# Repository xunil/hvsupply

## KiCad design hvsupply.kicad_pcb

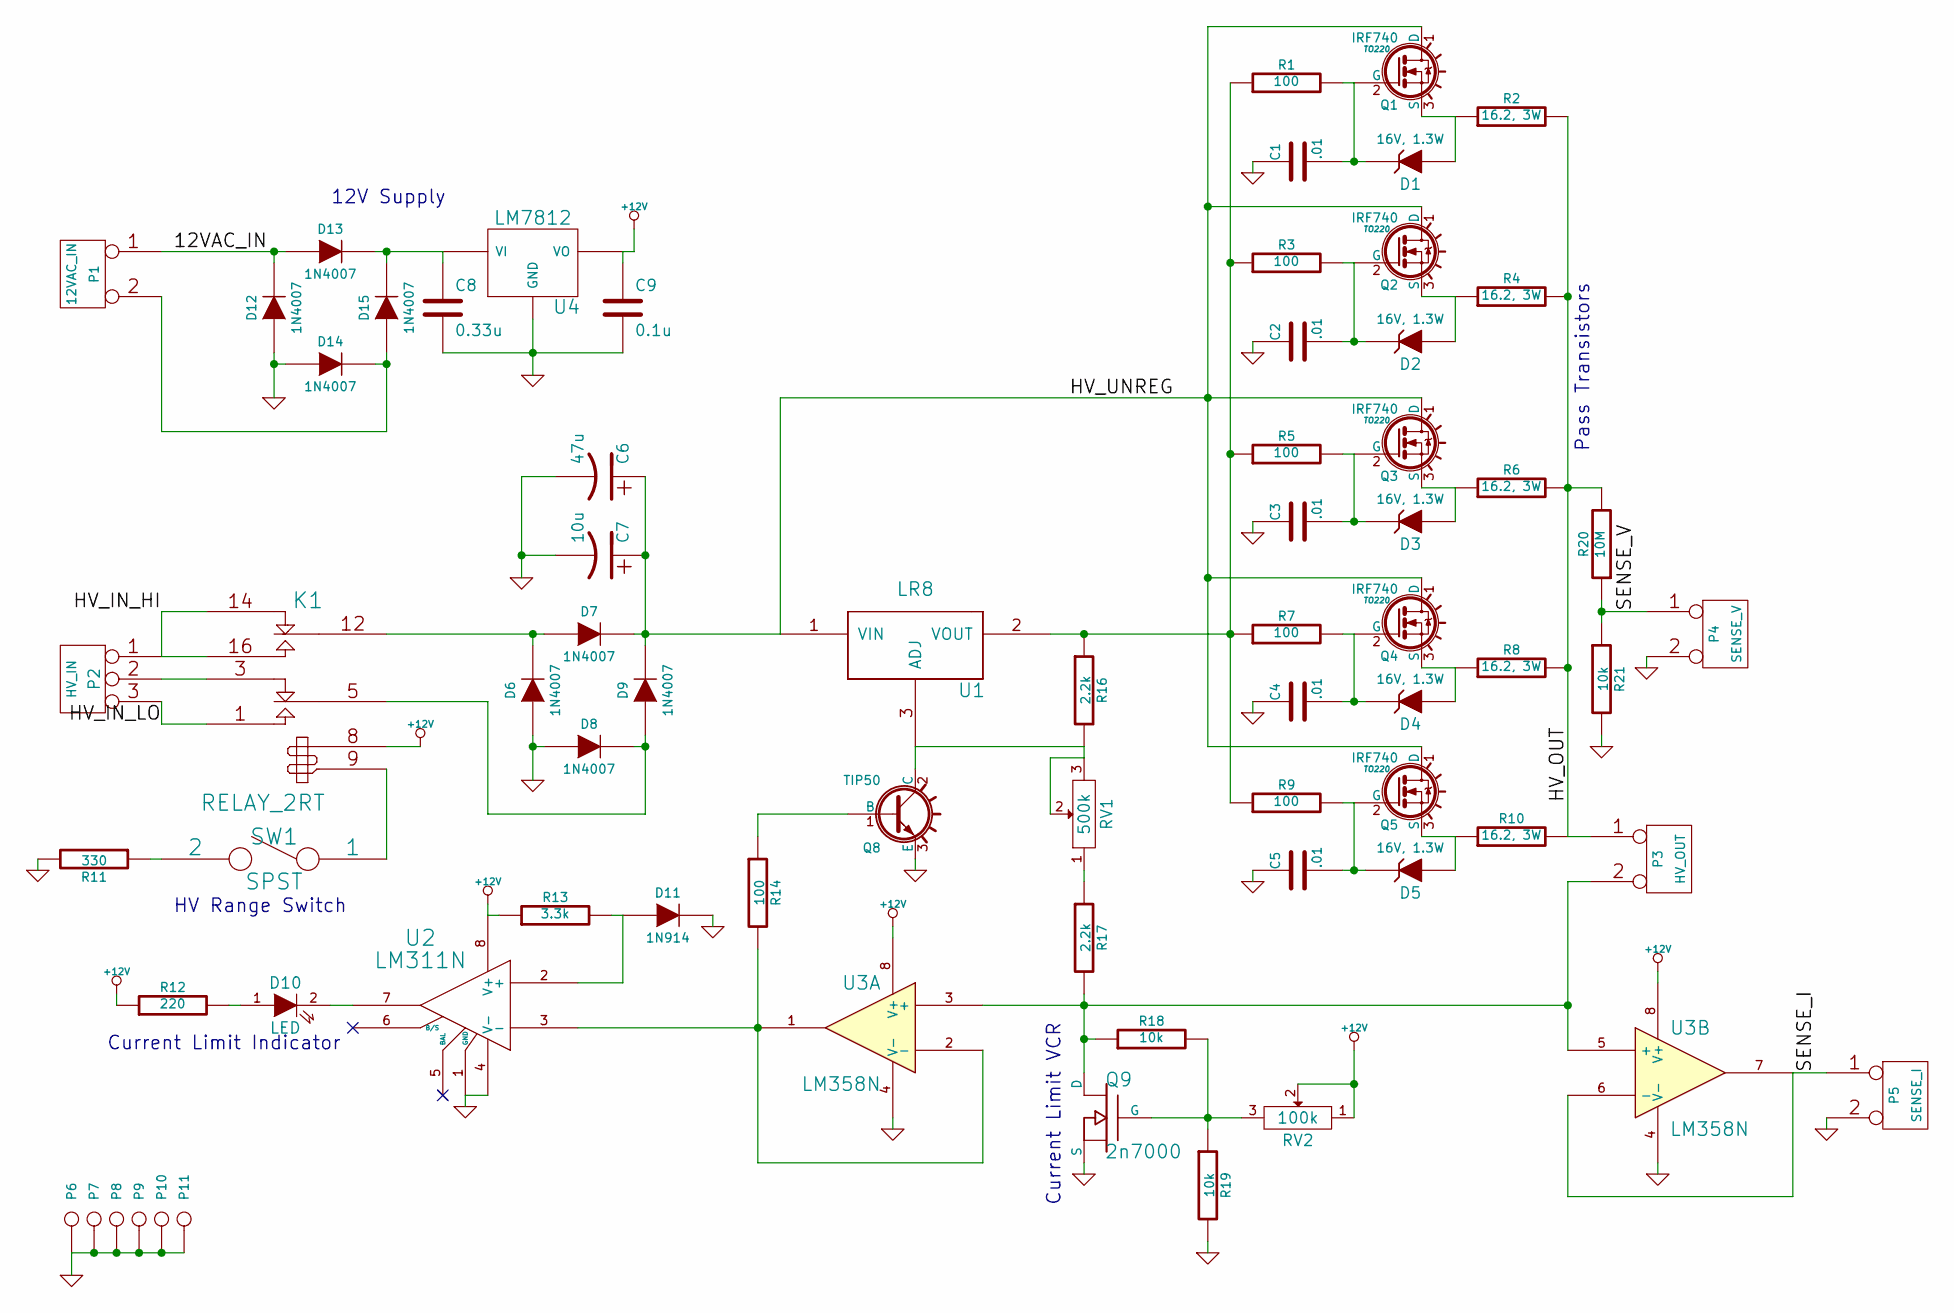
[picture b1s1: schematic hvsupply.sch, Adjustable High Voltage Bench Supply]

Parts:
C1, C2, C3, C4, C5: .01
C6: 47u
C7: 10u
C8: 0.33u
C9: 0.1u
D1, D2, D3, D4, D5: 16V, 1.3W
D6, D7, D8, D9: 1N4007
D10: LED
D11: 1N914
D12, D13, D14, D15: 1N4007
K1: RELAY_2RT
P1: 12VAC_IN
P2: HV_IN
P3: HV_OUT
P4: SENSE_V
P5: SENSE_I
P6, P7, P8, P9, P10, P11: CONN_1
Q1, Q2, Q3, Q4, Q5: IRF740; TO220
Q8: TIP50; TO220
Q9: 2n7000
R1, R3, R5, R7, R9: 100
R2, R4, R6, R8, R10: 16.2, 3W
R11: 330
R12: 220
R13: 3.3k
R14: 100
R16, R17: 2.2k
R18, R19, R21: 10k
R20: 10M
RV1: 500k
RV2: 100k
SW1: SPST
U1: LR8
U2: LM311N
U3: LM358N
U4: LM7812

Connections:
+12V: C9.1, K1.8, R12.1, R13.1, RV2.1, RV2.2, U2.8 (V+), U3.8 (V+), U4.VO
/12VAC_IN: D12.2 (K), D13.1 (A), P1.1
/HV_IN_HI: K1.14 (R2), K1.16 (T2), P2.1
/HV_IN_LO: K1.1 (T1), P2.3
/HV_OUT: P3.1, R2.2, R4.2, R6.2, R8.2, R10.2, R20.2
/HV_UNREG: C6.1, C7.1, D7.2 (K), D9.2 (K), Q1.1 (D), Q2.1 (D), Q3.1 (D), Q4.1 (D), Q5.1 (D), U1.1 (VIN)
/SENSE_I: P5.1, U3.6 (-), U3.7
/SENSE_V: P4.1, R20.1, R21.1
GND: C1.1, C2.1, C3.1, C4.1, C5.1, C6.2, C7.2, C8.2, C9.2, D6.1 (A), D8.1 (A), D11.2 (K), D12.1 (A), D14.1 (A), P4.2 (PM), P5.2 (PM), P6.1, P7.1, P8.1, P9.1, P10.1, P11.1, Q8.3 (E), Q9.S, R11.2, R19.2, R21.2, U2.1 (GND), U2.4 (V-), U3.4 (V-), U4.GND
unnamed: C1.2, D1.2 (K), Q1.2 (G), R1.2
unnamed: C2.2, D2.2 (K), Q2.2 (G), R3.2
unnamed: D10.1 (A), R12.2
unnamed: K1.9, SW1.1
unnamed: D5.1 (A), Q5.3 (S), R10.1
unnamed: C5.2, D5.2 (K), Q5.2 (G), R9.2
unnamed: D4.1 (A), Q4.3 (S), R8.1
unnamed: C4.2, D4.2 (K), Q4.2 (G), R7.2
unnamed: C3.2, D3.2 (K), Q3.2 (G), R5.2
unnamed: D3.1 (A), Q3.3 (S), R6.1
unnamed: D6.2 (K), D7.1 (A), K1.12 (C2)
unnamed: K1.3 (R1), P2.2 (PM)
unnamed: D2.1 (A), Q2.3 (S), R4.1
unnamed: D1.1 (A), Q1.3 (S), R2.1
unnamed: Q8.1 (B), R14.1
unnamed: C8.1, D13.2 (K), D15.2 (K), U4.VI
unnamed: Q9.G, R18.2, R19.1, RV2.3
unnamed: D10.2 (K), U2.7
unnamed: D14.2 (K), D15.1 (A), P1.2 (PM)
unnamed: D11.1 (A), R13.2, U2.2 (+)
unnamed: R14.2, U2.3 (-), U3.1, U3.2 (-)
unnamed: R11.1, SW1.2
unnamed: P3.2 (PM), Q9.D, R17.2, R18.1, U3.3 (+), U3.5 (+)
unnamed: Q8.2 (C), R16.2, RV1.2, RV1.3, U1.3 (ADJ)
unnamed: R17.1, RV1.1
unnamed: R1.1, R3.1, R5.1, R7.1, R9.1, R16.1, U1.2 (VOUT)
unnamed: D8.2 (K), D9.1 (A), K1.5 (C1)

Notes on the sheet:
Current Limit Indicator
Current Limit VCR
12V Supply
HV Range Switch
Pass Transistors

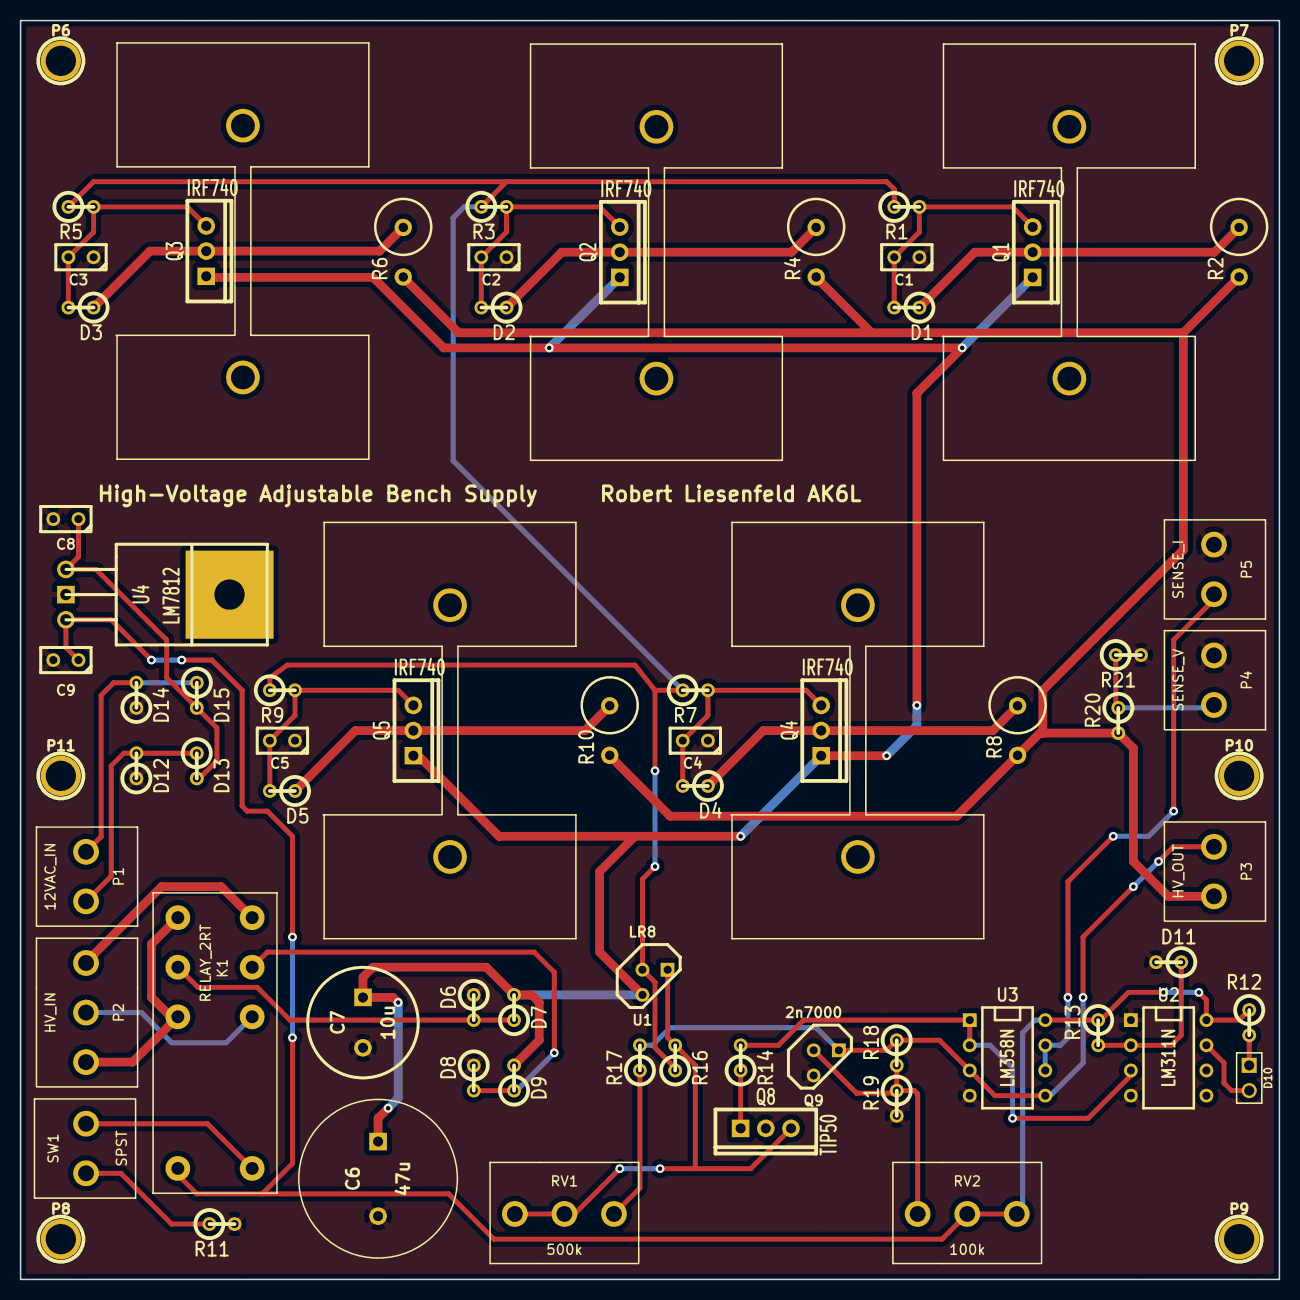
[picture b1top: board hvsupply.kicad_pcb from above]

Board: 2 copper layers, 127.0 x 127.0 mm, 70 parts (0 on the bottom side), 36 nets.

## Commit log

2013-05-14 Initial import
2013-07-07 Beginning to look like a PCB.
2013-07-13 Fixed circuit error, added VCR for current limit adjustment, prototyping current limit indicator.
2013-07-22 Major changes: unity-gain op-amps for current limit triggering and current sense buffering; comparator-based current limit indicator; voltage-controlled resistor-based adjustable current limit.
2013-08-01 Skip *bak files
2013-08-01 Started from scratch on the PCB. Parts placement mostly done.
2013-08-01 We don't need no stinking backup files.
2013-08-02 Most traces run. 12V supply section remains.
2013-08-02 Generated new drill files.
2013-08-02 Had to put something on the back silkscreen.
2013-12-22 Fixed anchor spacing for heatsinks, drill diameter for balance resistors.
2013-12-22 New gerbers for updated heatsink and balance resistor footprints
